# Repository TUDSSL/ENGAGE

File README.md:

# Battery-Free Game Boy

This is the official public repository for ENGAGE: the battery-free gaming console.
    
## Project Overview

### Rationale

Battery-free devices can [make phone calls](https://dl.acm.org/doi/abs/10.1145/3090090), [facilitate machine learning](https://dl.acm.org/doi/10.1145/3411808), or even [track eyes](https://doi.org/10.1145/3241539.3241578), but immersive interactive experience without batteries has not been explored so far. In this project we focus on this ignored part of the battery-free device ecosystem. We explore how reactive and user-centric applications, _mobile gaming_ in particular, can also be battery-free.	

### The Basic Problem of Gaming without Batteries: Power Failures 

Powering small embedded computer only with energy harvesting would cause frequent power failures, resulting in a constant restart of a long-running application. Let us look at the above figure which symbolically represents an execution of a [Tetris](https://en.wikipedia.org/wiki/Tetris) game on a battery-free platform powered by harvested (fluctuating) energy. Without any protection against power failures the game would play until energy is lost (i.e. at line 185) and then would restart from the loading screen. [Intermittent computing techniques](https://drops.dagstuhl.de/opus/volltexte/2017/7131/pdf/LIPIcs-SNAPL-2017-8.pdf) would protect from this unwanted behaviour: after a power failure, line 186 would be executed proceeding from the exact system state as before the power failure. This way a game state will resume at the exact frame where the play ended due to power failure (in other words, [tetromino](https://en.wikipedia.org/wiki/Tetromino) will be in the same place when the game resumes).

### System Design: Game Boy Emulation and System State Checkpointing

We designed a Nintendo Game Boy emulator, which we call _Energy Aware Gaming (ENGAGE)_ platform, as a proof of concept that interactive systems powered by only by (intermittently-available) energy harvesting is possible. ENGAGE is build around four key components (see also figure above):

1. **Game emulation:** Use processor emulation to play (Game Boy) retro games to resemble classic [Game Boy](https://en.wikipedia.org/wiki/Game_Boy) platform feel;
1. **Kernel:** Efficiently checkpoint minimal game state to the dedicated non-volatile memory to protect from a restart after a power failure, enabling continuous game play;
1. **Energy:** Power battery-free gaming console from gaming actions (button presses) and from ambient solar energy and store this energy in a small capacitor;
1. **Hardware:** Exploit leading (but off-the-shelf and accessible to everyone) [low-power 32-bit ARM Cortex M4 microcontroller](https://ambiq.com/apollo3-blue/) and [external FRAM](https://www.fujitsu.com/global/documents/products/devices/semiconductor/fram/lineup/MB85RS4MT-DS501-00053-1v0-E.pdf) to support checkpointing system.

### Hardware

ENGAGE internal PCB is depicted on the above figure (left-hand side: front, right-hand side: back) with the main components (A) [Ambiq Apollo3 Blue ARM Cortex-M4 MCU](https://ambiq.com/apollo3-blue/), (B) [Fujitsu MB85RS4MT 512 KB FRAM](https://www.fujitsu.com/global/documents/products/devices/semiconductor/fram/lineup/MB85RS4MT-DS501-00053-1v0-E.pdf), (C) [ZF AFIG-0007 energy harvesting switch](https://nl.mouser.com/datasheet/2/833/Energy_Harvesting_Generator_US-1075748.pdf), (D) [Semiconductor Components Industries NSR1030QMUTWG low forward voltage diode bridge](https://www.onsemi.com/pub/Collateral/NSR1030QMU-D.PDF), (E) micro USB debugging port, (F) display connector, (G) solar panels connector, (H) cartridge interface, (I) [Texas Instruments BQ25570 harvester/power manager](https://www.ti.com/lit/ds/symlink/bq25570.pdf), and (J) [Texas Instruments TPS61099 boost converter](https://www.ti.com/lit/ds/symlink/tps61099.pdf).

The specific internals of ENGAGE are as follows.

**Microcontroller:** ENGAGE is based on [ARM MCU architecture](https://en.wikipedia.org/wiki/ARM_architecture), a departure from [Texas Instruments MSP430 FRAM series](https://www.ti.com/lit/an/slaa498b/slaa498b.pdf) microcontrollers typically used in [intermittent computing systems](https://drops.dagstuhl.de/opus/volltexte/2017/7131/pdf/LIPIcs-SNAPL-2017-8.pdf). Specifically, we have used [Ambiq Apollo3 Blue ARM Cortex-M4](https://ambiq.com/apollo3-blue/) (operating at a clock frequency of 96 MHz) chosen for its best-in-class energy efficiency. Apollo3 MCU (marked as (A) in the above figure) runs the Game Boy emulator and [checkpointing software](https://github.com/TUDSSL/ENGAGE/tree/master/software).

**Memory:** A fast, byte-addressable, non-volatile memory is crucial to enable saving and restoring ENGAGE state (in other words, game state) in spite of power failures. To enable this, we equipped ENGAGE with an external dedicated FRAM IC: [Fujitsu MB85RS4MT 512 KB FRAM](https://www.fujitsu.com/global/documents/products/devices/semiconductor/fram/lineup/MB85RS4MT-DS501-00053-1v0-E.pdf), marked as (B) in the above figure, connected through SPI to the MCU providing a fast (enough) and durable method of non-volatile storage for checkpoints.

**Energy Harvesting:** We extract energy from two sources: (i) button presses, using six mechanical off-the-shelf [ZF AFIG-0007 energy harvesting switches](https://nl.mouser.com/datasheet/2/833/Energy_Harvesting_Generator_US-1075748.pdf) - four switches at the D-pad and one switch per "A" and "B" button (see (C) in the above figure), and (ii) a set of [Panasonic AM-1417CA amorphous silicon solar cells](https://www.panasonic-electric-works.com/cps/rde/xbcr/pew_eu_en/ca_amorton_solar_cells_en.pdf) attached to the front of the Game Boy chassis. Solar panels are managed by [Texas Instruments BQ25570 harvester/power manager](https://www.ti.com/lit/ds/symlink/bq25570.pdf). Harvested energy is stored in a 3.3 mF capacitor.

**Cartridges:** To be able to read Game Boy game cartridges, a cartridge connector is placed on the back of the ENGAGE platform PCB (marked as (H) in the above figure). The cartridge interfaces with the MCU using [Semtech SX1503 I/O expanders](https://www.mouser.com/datasheet/2/761/sx150x-1283306.pdf). This extender translates the 3V system voltage to 5V logic required by the cartridge.

**Display:** It was difficult to source a large display that had reasonable power requirements, a decent refresh rate, and minimal external driving circuitry. We quickly discarded the use of electronic ink displays because of its slow refresh rate and complex driving circuitry. Instead we use a 26.02 × 27.82 mm [Japan Display LPM013M126A LCD](https://www.j-display.com/product/pdf/Datasheet/4LPM013M126A_specification_Ver02.pdf). The display is is smaller than the original Game Boy screen (47 × 43 mm) but has a better resolution of 176 × 176 pixels compared to original 160 × 144 pixel matrix.

### Checkpointing

The core software component of ENGAGE is differential checkpointing library called _MPatch_ located in [software/libs/mpatch](https://github.com/TUDSSL/ENGAGE/blob/master/software/libs/mpatch) folder of this repository. Further description of MPatch is provided in a separate [document](https://github.com/TUDSSL/ENGAGE/blob/master/software/libs/mpatch/README.md).

## Getting Started

This repository contains everything required to build your own Battery-Free Game Boy. Below we describe how to build your own ENGAGE hardware and software.

### Building the Hardware

Hardware-related sources are stored in the following folders.

 - [/enclosure](https://github.com/TUDSSL/ENGAGE/tree/master/enclosure): Complete set of [3D STL files](https://en.wikipedia.org/wiki/STL_%28file_format%29) of the complete ENGAGE enclosure (front, back, buttons, D-pad, LCD holder)
 - [/hardware/main-board](https://github.com/TUDSSL/ENGAGE/tree/master/hardware/main-board): Main ENGAGE board [KiCad](https://kicad.org/) files. Specifically, the folder contains `.gbr` Gerber output files for manufacturing, `.drl` drill file for manufacturing, schematics of the PCB in `.pdf` format, `.csv` file with bill of materials and the KiCad project files `.kicad_pcb`, `.pro` and `.sch`.
 - [/hardware/apollo-3-module](https://github.com/TUDSSL/ENGAGE/tree/master/hardware/apollo-3-module): As above, but for the de-attachable board with the MCU and FRAM (see above figure - component (A) and (B))
 
 Enclosure can be printed using your favorite 3D printer or you can send all [/enclosure](https://github.com/TUDSSL/ENGAGE/tree/master/enclosure) files to one of online-available 3D printing services. As for the PCBs, you can either assemble everything yourself or send all [/hardware](https://github.com/TUDSSL/ENGAGE/tree/master/hardware/) files to many online-available PCB assembly companies for production. 

### Building the Software

Software-related sources are stored in the following folders.

- [/software/apps](https://github.com/TUDSSL/ENGAGE/tree/master/software/apps): Applications' source code folder containing three applications:
    - [emulator](https://github.com/TUDSSL/ENGAGE/tree/master/software/apps/emulator): main application of ENGAGE emulator, which can be also used to reproduce [results of the paper](#How-to-Cite-This-Work);
    - [checkpoint](https://github.com/TUDSSL/ENGAGE/tree/master/software/apps/checkpoint): application to test the performance of checkpointing mechanism;
    - [memtracker](https://github.com/TUDSSL/ENGAGE/tree/master/software/apps/memtracker): application to test the performance of memory use tracking mechanism;
- [/software/config](https://github.com/TUDSSL/ENGAGE/tree/master/software/config): Various configuration files.
- [/software/external](https://github.com/TUDSSL/ENGAGE/tree/master/software/external): External dependencies to the project, such as MCU SDK.
- [/software/libs](https://github.com/TUDSSL/ENGAGE/tree/master/software/libs): Set of core libraries handling I/O (that is [console buttons](https://github.com/TUDSSL/ENGAGE/tree/master/software/libs/buttons), [game cartridge](https://github.com/TUDSSL/ENGAGE/tree/master/software/libs/cartridge), [console display](https://github.com/TUDSSL/ENGAGE/tree/master/software/libs/display), [Game Boy emulator](https://github.com/TUDSSL/ENGAGE/tree/master/software/libs/emulator), [FRAM access](https://github.com/TUDSSL/ENGAGE/tree/master/software/libs/fram)) and checkpointing (that is [just-in-time checkpoint](https://github.com/TUDSSL/ENGAGE/tree/master/software/libs/jit), [memory state tracker](https://github.com/TUDSSL/ENGAGE/tree/master/software/libs/memtracker), and [MPatch checkpointing](https://github.com/TUDSSL/ENGAGE/tree/master/software/libs/mpatch)).
- [/software/platforms](https://github.com/TUDSSL/ENGAGE/tree/master/software/platforms): GPIO pin mappings.
- [/software/scripts](https://github.com/TUDSSL/ENGAGE/tree/master/software/scripts): Scripts pertaining to the build process.

#### Note on the Game Boy Emulator

We do not provide the copy of the Game Boy emulator in this repository. Our build system (using [/software/scripts](https://github.com/TUDSSL/ENGAGE/tree/master/software/scripts)) automatically downloads and patches (applying optimizations and improvements) an external, not written by us, Game Boy emulator. Specifically, we have used [Game Boy emulator](https://mikrocontroller.bplaced.net/wordpress/?page_id=1290) for [STM32F746 Discovery board](https://www.st.com/en/evaluation-tools/32f746gdiscovery.html) written by [Uwe Becker](https://mikrocontroller.bplaced.net/wordpress/?page_id=8).

#### Build Process

After cloning this repository to your local computer the following instructions can be used to generate the ENGAGE binaries. From the project directory execute the following.

```bash
$ cd software/build
$ cmake ..
$ make install

```

Then using your favorite debugger (we have used one of [SEGGER J-Link debug probes](https://www.segger.com/products/debug-probes/j-link/models/model-overview/) for this project) the ENGAGE binaries (stored in the [/software/bin](https://github.com/TUDSSL/ENGAGE/tree/master/software/bin) folder) can be uploaded to the MCU using a debugger whilst powering the platform using USB. The main binary is called `emulator` whilst the others provide a means to reproduce the results obtained in the [paper](#How-to-Cite-This-Work). After this step a [game cartridge can be loaded](#Load-Game-Cartridge).

#### Last Tested Software Versions

This software was build successfully using the following software versions.

- [CMake](https://cmake.org/download/) version 3.18.4
- [arm-none-eabi-gcc](https://gcc.gnu.org/) version 10.2.0
- [arm-none-eabi-newlib](https://www.sourceware.org/newlib/) version 3.3.0
- [arm-none-eabi-binutils](https://www.gnu.org/software/binutils/) version 2.35

## How to Operate ENGAGE

There are two important operations when using ENGAGE that are not related to normal gaming: **loading game cartridge** and **system reset**, both described below.

### Load Game Cartridge

After programming the [emulator binary](https://github.com/TUDSSL/ENGAGE/tree/master/software/bin) to ENGAGE, a Game Boy cartridge with your favorite game needs to be loaded to ENGAGE. To load a cartridge, first put the physical cartridge in the cartridge slot (at the back of ENGAGE) and then hold down **Start** and **A** buttons on ENGAGE while powering ENGAGE through the USB port. You can let go **Start** and **A** buttons after a few seconds. When loading of the cartridge has completed the game will start. Note that there is currently [no progress indication](https://github.com/TUDSSL/ENGAGE/issues/4) of this operation on the screen of ENGAGE. Remember that the process can take five minutes (or more) for large cartridges! After a cartridge has been loaded it can be removed from the device.

### System Reset

Due to the unique nature of ENGAGE's state resuming after power failure, resetting ENGAGE requires a unique key combination (unlike the original Game Boy that you could turn off and on again easily). This reset is performed by holding **Start** and **Select** buttons while powering ENGAGE through an USB port. Please note that this reset operation does *not* require you to reload the game cartridge.

## Frequently Asked Questions

- **When the energy source is changed from solar to button-mashing, how long is ENGAGE temporarily off?**

We actually harvest from both energy sources at the same time! We developed a circuit that manages this internally. However, this still means that the user will experience interruptions of play, that can vary between sub-second (in extreme well outdoor light conditions) to many seconds (on a gloomy day, indoors). While the button presses generate extra energy to sustain game play, most of the energy is still generated by solar panels. More discussion on this can be found in our [research paper](#How-to-Cite-This-Work). 

- **How do the buttons generate power?**

The buttons generate power by moving a small but powerful magnet inside a tightly wound wire coil. The change in the magnetic field generates power. When you press the button (and when you release) it moves the magnet through the coil, this energy is then siphoned into a capacitor for immediate use by the ENGAGE hardware to support all activities. Because of advances in manufacturing over the past decade the magnet and coil are so small that they can fit inside a button that is acceptable to a user.

- **Why is the screen so small?**

Yes, the screen is smaller that in the original Game Boy (which is a [source of complaints](https://www.reddit.com/r/gadgets/comments/in3aco/batteryfree_game_boy_runs_off_of_solar_and/) of many internauts), but the one we [used in the initial ENGAGE design](https://www.j-display.com/product/pdf/Datasheet/4LPM013M126A_specification_Ver02.pdf) the best one we could find in terms of resolution and energy consumption. If you have a better screen to suggest, then make a new [project issue](#How-to-Contribute-to-this-Project) and send us a [pull request](#How-to-Contribute-to-this-Project).

- **Can ENGAGE play sound?**

Unfortunately not. Sound generation costs extra energy and as we operate on a very thin energy budget we had to make choices which features of original Game Boy had to be excluded from ENGAGE.

- **Can I buy one?**

Unfortunately not. But you can build one! All hardware and software of ENGAGE, together with the process of how to make it run is simply in _this repository_. Please remember that ENGAGE **was not (and is not meant to be) a product we can sell**. This is a research project and a concept demonstration.

## How to Contribute to this Project

We look forward to your contributions, improvements, additions and changes. Please follow the standard [GitHub flow](https://docs.github.com/en/free-pro-team@latest/github/collaborating-with-issues-and-pull-requests/github-flow) for code contributions. In macro terms this means the following.

1. [Fork the `master` branch](https://docs.github.com/en/free-pro-team@latest/github/getting-started-with-github/fork-a-repo#keep-your-fork-synced)  of this repository; make sure that your fork will be [up to date](https://docs.github.com/en/free-pro-team@latest/github/getting-started-with-github/fork-a-repo#keep-your-fork-synced) with the latest `master` branch.
1. Create an issue [here](https://github.com/TUDSSL/ENGAGE/issues) with a new feature or a bug report.
1. Perform changes on your local branch and [push them to your forked clone](https://docs.github.com/en/free-pro-team@latest/github/collaborating-with-issues-and-pull-requests/merging-an-upstream-repository-into-your-fork).
1. Create a [pull request](https://docs.github.com/en/free-pro-team@latest/github/collaborating-with-issues-and-pull-requests/creating-a-pull-request) referencing the issue it covers and wait for our response.

### List of Known Issues

List of all known issues is listed in the [Issues](https://github.com/TUDSSL/ENGAGE/issues) list of this project. If you found a bug or you would like to enhance ENGAGE: [please contribute](#How-to-Contribute-to-this-Project)! We look forward to your additions. Let ENGAGE grow and become a better and **more sustainable** gaming experience.

## How to Cite This Work

The results of this project have been published in a peer-reviewed academic publication (from which all technical figures in this file originate). Details of the publication are as follows.

* **Authors and the project team:** [Jasper de Winkel](https://jasperdewinkel.com/), [Vito Kortbeek](https://www.vitokortbeek.com/), [Josiah Hester](https://josiahhester.com/), [Przemysław Pawełczak](http://www.pawelczak.net/)
* **Publication title:** _Battery-Free Game Boy_
* **Pulication venue:** [Proceedings of the ACM on Interactive, Mobile, Wearable and Ubiquitous Technologies, Volume 4, Issue 3, September 2020](https://dl.acm.org/toc/imwut/2020/4/3) and [Proceedings of ACM UbiComp 2020](https://ubicomp.org/ubicomp2020/)
* **Link to publication:** https://doi.org/10.1145/3411839 (Open Access)
* **Link to ACM UbiComp 2020 conference presentation video:** https://www.youtube.com/watch?v=XxjrTHBFBSM

To cite this publication please use the following BiBTeX entry.

```
@article{dewinkel:imwut:2020:gameboy,
  title = {Battery-Free Game Boy},
  author = {Jasper {de Winkel} and Vito {Kortbeek} and Josiah {Hester} and Przemys{\l}aw {Pawe{\l}czak}},
  journal = {Proc. ACM Interact. Mob. Wearable Ubiquitous Technol.},
  volume = {4},
  number = {3},
  pages = {111:1--111:34},
  year = {2020},
  publisher = {ACM}
}
```

## Related Websites

* **Project source code:** https://github.com/tudssl/engage (this repository)
* **Project announcement website:** https://www.freethegameboy.info

## The Press

The project has been covered extensively by international media. Here is the list of example posts and articles (as of October 30, 2020).

[CNET](https://www.cnet.com/features/the-first-battery-free-game-boy-wants-to-power-a-gaming-revolution/), [The Wall Street Journal](https://www.wsj.com/articles/battery-free-energy-harvesting-perpetual-machines-the-weird-future-of-computing-11601697600?st=xyjz99iomamhwr6&reflink=article_copyURL_share), [Mashable](https://mashable.com/video/battery-free-gameboy/), [Hackaday](https://hackaday.com/2020/09/11/game-boy-plays-forever/), [The Verge](https://www.theverge.com/tldr/2020/9/4/21422605/engage-battery-free-game-boy-button-mashing-solar-panels-research-environmental-sustainability), [Gizmodo](https://earther.gizmodo.com/this-battery-free-game-boy-is-the-first-step-toward-ens-1844953062), [Engadget](https://www.engadget.com/engage-game-boy-211023869.html), [PCMag](https://www.pcmag.com/news/solar-powered-game-boy-provides-infinite-play), [The Register](https://www.theregister.com/2020/09/04/battery_free_gameboy/), [Tech Times](https://www.techtimes.com/articles/252268/20200903/game-boy-gaming-console-battery-free-play-want-without-recharging.htm), [Nintendo Life](https://www.nintendolife.com/news/2020/09/this_battery-free_game_boy_could_be_the_future_of_portable_tech), [Daily Mail](https://www.dailymail.co.uk/sciencetech/article-8695791/Battery-free-Game-Boy-charged-MILLIONS-times-sun-pressing-buttons.html), [The Independent](https://www.independent.co.uk/life-style/gadgets-and-tech/news/game-boy-battery-free-technology-renewable-power-a9705256.html), [r/gadgets](https://www.reddit.com/r/gadgets/comments/in3aco/batteryfree_game_boy_runs_off_of_solar_and/)

## Acknowledgments

This research project was supported by [Netherlands Organisation for Scientific Research](https://www.nwo.nl/en), partly funded by the [Dutch Ministry of Economic Affairs and Climate Policy](https://www.government.nl/ministries/ministry-of-economic-affairs-and-climate-policy), through [TTW Perspective program ZERO (P15-06)](https://www.nwo.nl/en/researchprogrammes/perspectief/previous-awards/zero-towards-energy-autonomous-systems-iot) within Project P1 and P4, and by the [National Science Foundation](https://www.nsf.org/) through grants [CNS-1850496](https://www.nsf.gov/awardsearch/showAward?AWD_ID=1850496) and [CNS-2032408](https://www.nsf.gov/awardsearch/showAward?AWD_ID=2032408). Any opinions, findings, and conclusions or recommendations expressed in this material are those of the author(s) and do not necessarily reflect the views of the National Science Foundation.

## Copyright

Copyright (C) 2020 TU Delft Embedded and Networked Systems Group/Sustainable Systems Laboratory.

MIT License or otherwise specified. See [license](https://github.com/TUDSSL/ENGAGE/blob/master/LICENSE) file for details.

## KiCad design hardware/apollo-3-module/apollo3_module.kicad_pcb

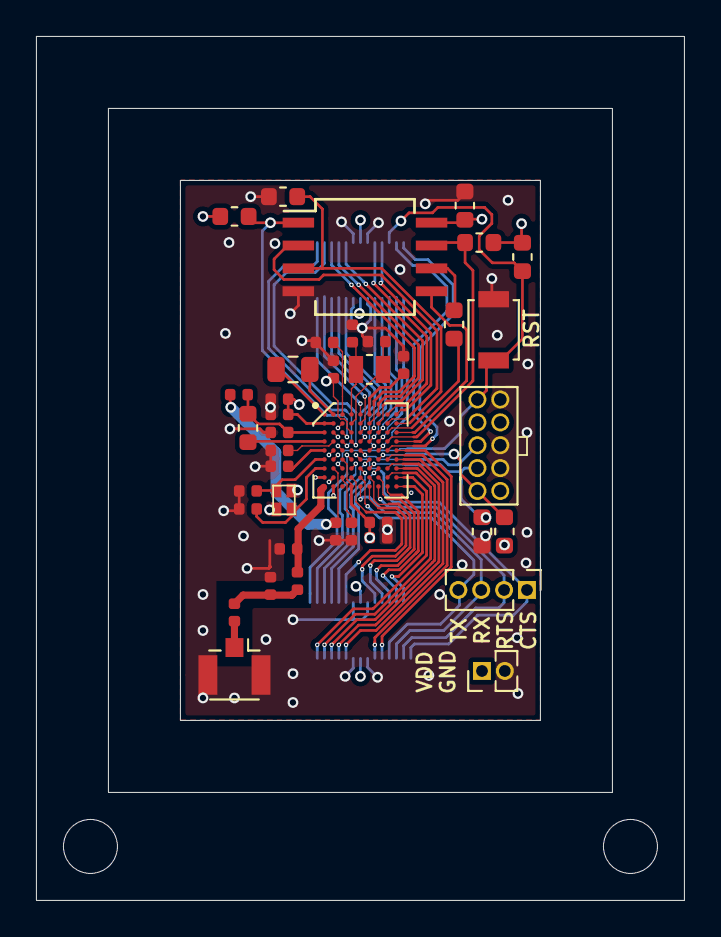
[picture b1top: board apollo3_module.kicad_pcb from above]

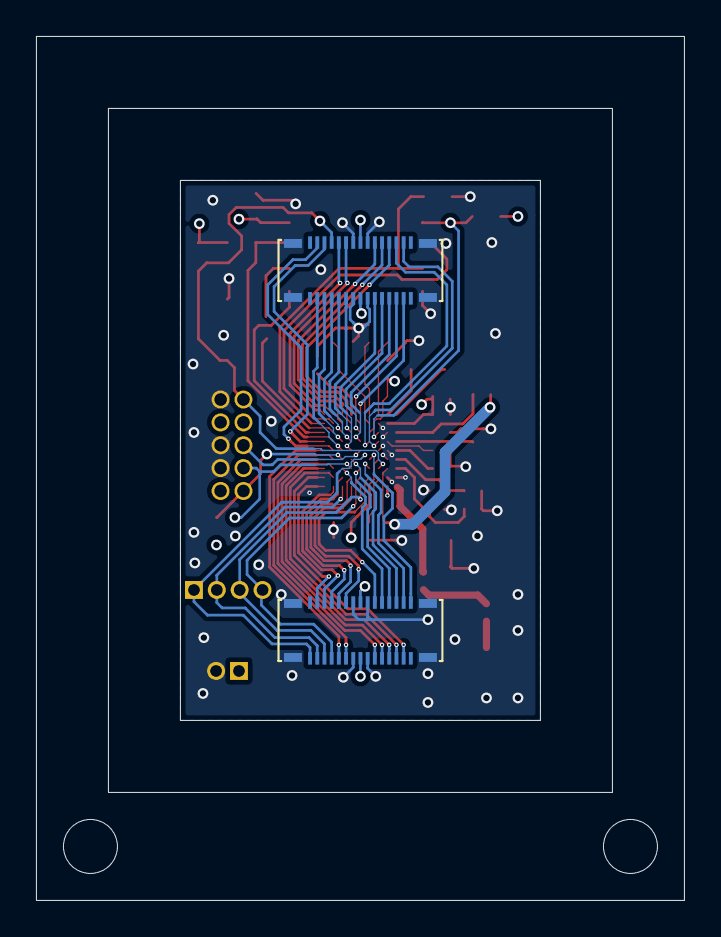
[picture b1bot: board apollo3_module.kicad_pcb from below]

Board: 4 copper layers, 36.0 x 48.0 mm, 44 parts (2 on the bottom side), 71 nets.

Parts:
C1, C5, C10, C11, C15: 1uF; C_0402_1005Metric
C2, C4, C13, C17, C18: DNP; C_0402_1005Metric
C3: 470nF; C_0402_1005Metric
C6: 47nF; C_0402_1005Metric
C7, C8, C9, C16: 2.2uF; C_0402_1005Metric
C12: 0.5pF; C_0402_1005Metric
C14: 4.7uF; C_0402_1005Metric
C19: 1uF; C_0603_1608Metric
H1, H2: eC_Registration; eC_Mount
J1, J2: 51338-0374
J3: Conn_01x04; PinHeader_1x04_P1.27mm_Vertical
J4: SWD_10; FTSH-105-01-F-D-K
J5: Conn_Coaxial; U.FL_Hirose_U.FL-R-SMT-1_Vertical
J6: Conn_01x02; PinHeader_1x02_P1.27mm_Vertical
L1: 2.2uH; L_0805_2012Metric
L2: 1uH; L_0603_1608Metric
L3: 2.7nH; L_0402_1005Metric
L4: 2nH; L_0402_1005Metric
R1: 0; R_0603_1608Metric
R2, R6, R7, R8: DNP; R_0603_1608Metric
R3: 0; R_0402_1005Metric
R4, R5: 10k; R_0603_1608Metric
SW1: B3U-1000P; SW_SPST_B3U-1000P
U1: APOLLO3; BGA-81_9x9_5.0x5.0mm
U2: MB85RS4MT; SO-8_5.3x6.2mm_P1.27mm
Y1: ECS-320-8-47-JTN; ECX-1247
Y2: ABS06W-32.678kHz-D-2; Crystal_SMD_MicroCrystal_CC8V-T1A-2Pin_2.0x1.2mm

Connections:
/DBG_CTS: J1.29, J3.1, U1.F5
/DBG_RTS: J1.27, J3.2, U1.J7
/DBG_RX: J1.25, J3.3, U1.J5
/DBG_TX: J1.23, J3.4, U1.H5
/FRAM_HOLD: R6.2, U1.D8, U2.7
/FRAM_WP: R7.1, U1.B9, U2.3
/G0: J1.12, U1.H4
/G1: J1.4, U1.G4
/G2: J1.2, U1.F4
/G3: J1.8, U1.G5
/G4: J2.26, U1.D9
/G5: J1.21, U1.E9
/G6: J2.28, U1.E8
/G7: J1.11, U1.F9
/G8: J1.19, U1.F8
/G9: J1.10, U1.G7
/G10: J1.9, U1.G8
/G11: J2.5, U1.B5
/G12: J2.10, U1.A7
/G13: J2.12, U1.B7
/G14: J2.25, U1.D7
/G15: J2.23, U1.C7
/G16: J2.6, U1.D4
/G17: J2.4, U1.D3
/G18: J2.9, U1.C5
/G25: J2.20, U1.A8
/G28: J2.22, U1.A9
/G29: J2.3, U1.A5
/G30: J1.6, U1.F6
/G31: J2.7, U1.D5
/G32: J2.11, U1.E6
/G33: J2.8, U1.B6
/G34: J2.19, U1.C6
/G35: J2.21, U1.D6
/G36: J1.22, U1.H6
/G37: J1.24, U1.H7
/G38: J1.20, U1.J6
/G39: J1.26, U1.J8
/G40: J1.28, U1.J9
/G46: J2.27, U1.E7
/G47: J1.3, U1.H9
/G48: J1.7, U1.G9
/G49: J1.5, U1.H8
/MSPI_CE0: R8.2, U1.C3, U2.1
/MSPI_CLK: R1.2, U2.6
/MSPI_MISO: U1.B8, U2.2
/MSPI_MOSI: U1.C9, U2.5
/SWDCK: J4.4, R4.1, U1.G6
/SWDIO: J4.2, R5.2, U1.F7
/SWO: J4.6, U1.E5
/nRST: J2.24, J4.10, R2.2, SW1.1, U1.G3
GND: C1.1, C2.2, C3.2, C4.2, C5.1, C6.2, C7.1, C8.1, C9.1, C10.1, C11.1, C12.2, C13.2, C14.2, C15.2, C16.1, C17.2, C18.1, C19.1, J1.13, J1.14, J1.17, J1.18, J1.31, J2.13, J2.14, J2.17, J2.18, J2.31, J4.3, J4.5, J4.9, J5.2, J6.2, R4.2, R7.2, SW1.2, U1.B3, U1.C2, U1.E2, U1.E3, U1.F2, U1.H1, U1.H2, U1.J2, U2.4, Y1.2, Y1.4
unnamed: C2.1, U1.G1, Y1.1
unnamed: C3.1, U1.A6
unnamed: C4.1, L3.1, U1.J1
unnamed: C6.1, U1.H3
unnamed: C7.2, U1.A3
unnamed: C8.2, U1.D2
unnamed: C9.2, U1.E1
unnamed: C12.1, L3.2, L4.1
unnamed: C13.1, U1.F1, Y1.3
unnamed: C14.1, L2.2, R3.1, U1.C1
unnamed: C15.1, R3.2, U1.G2
unnamed: C17.1, U1.A4, Y2.1
unnamed: C18.2, U1.B4, Y2.2
unnamed: J5.1, L4.2
unnamed: L1.1, U1.A1
unnamed: L1.2, U1.A2
unnamed: L2.1, U1.D1
unnamed: R1.1, U1.C8
VDD: C1.2, C5.2, C10.2, C11.2, C16.2, C19.2, J1.15, J1.16, J2.15, J2.16, J4.1, J6.1, R2.1, R5.1, R6.1, R8.1, U1.B1, U1.B2, U1.C4, U1.F3, U1.J4, U2.8

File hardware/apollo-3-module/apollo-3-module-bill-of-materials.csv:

Item,Qty,Reference(s),Value,Datasheet,Partnum
1,5,"C1, C5, C10, C11, C15",1uF,~,GRM155C81A105KA12D
2,5,"C2, C4, C13, C17, C18",DNP,~,
3,1,C3,470nF,~,GRT155R61C474KE01D
4,1,C6,47nF,~,GRM155R71E473KA88D
5,4,"C7, C8, C9, C16",2.2uF,~,GRM155R61C225KE11D
6,1,C12,0.5pF,~,GRM1885C1HR50BA01D
7,1,C14,4.7uF,~,CL05A475KP5NRNC
8,1,C19,1uF,~,TMK107B7105KA-T
9,2,"H1, H2",eC_Registration,https://www.eurocircuits.com/ec-registration-system/,
10,2,"J1, J2",51338-0374,https://www.molex.com/webdocs/datasheets/pdf/en-us/051338037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,51338-0374
11,1,J3,Conn_01x04,~,GRPB041VWVN-RC
12,1,J4,SWD_10,http://infocenter.arm.com/help/topic/com.arm.doc.ddi0314h/DD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,FTSH-105-01-F-D-K
13,1,J5,Conn_Coaxial, ~,U.FL-R-SMT-1
14,1,J6,Conn_01x02,~,GRPB021VWVN-RC
15,1,L1,2.2uH,~,DFE201610E-2R2M=P2
16,1,L2,1uH,~,DFE18SAN1R0MG0L
17,1,L3,2.7nH,~,LQG15HS2N7S02D
18,1,L4,2nH,~,LQG15HS2N0S02D
19,1,R1,0,~,ERJ-3GEY0R00V
20,4,"R2, R6, R7, R8",DNP,~,
21,1,R3,0,~,ERJ-2GE0R00X
22,2,"R4, R5",10k,~,ERJ-3GEYJ103V
23,1,SW1,B3U-1000P,~,B3U-1000P
24,1,U1,APOLLO3,https://www.ambiqmicro.com/static/mcu/files/Apollo3_Blue_MCU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,AMA3B1KK-KBR-B0
25,1,U2,MB85RS4MT,https://www.fujitsu.com/global/documents/products/devices/se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,MB85RS4MT
26,1,Y1,ECS-320-8-47-JTN,https://nl.mouser.com/datasheet/2/122/ECX_1247-220263.pdf,ECS-320-8-47-JTN
27,1,Y2,ABS06W-32.678kHz-D-2,https://abracon.com/Resonators/ABS06W.pdf,ABS06W-32.768kHz-D-2

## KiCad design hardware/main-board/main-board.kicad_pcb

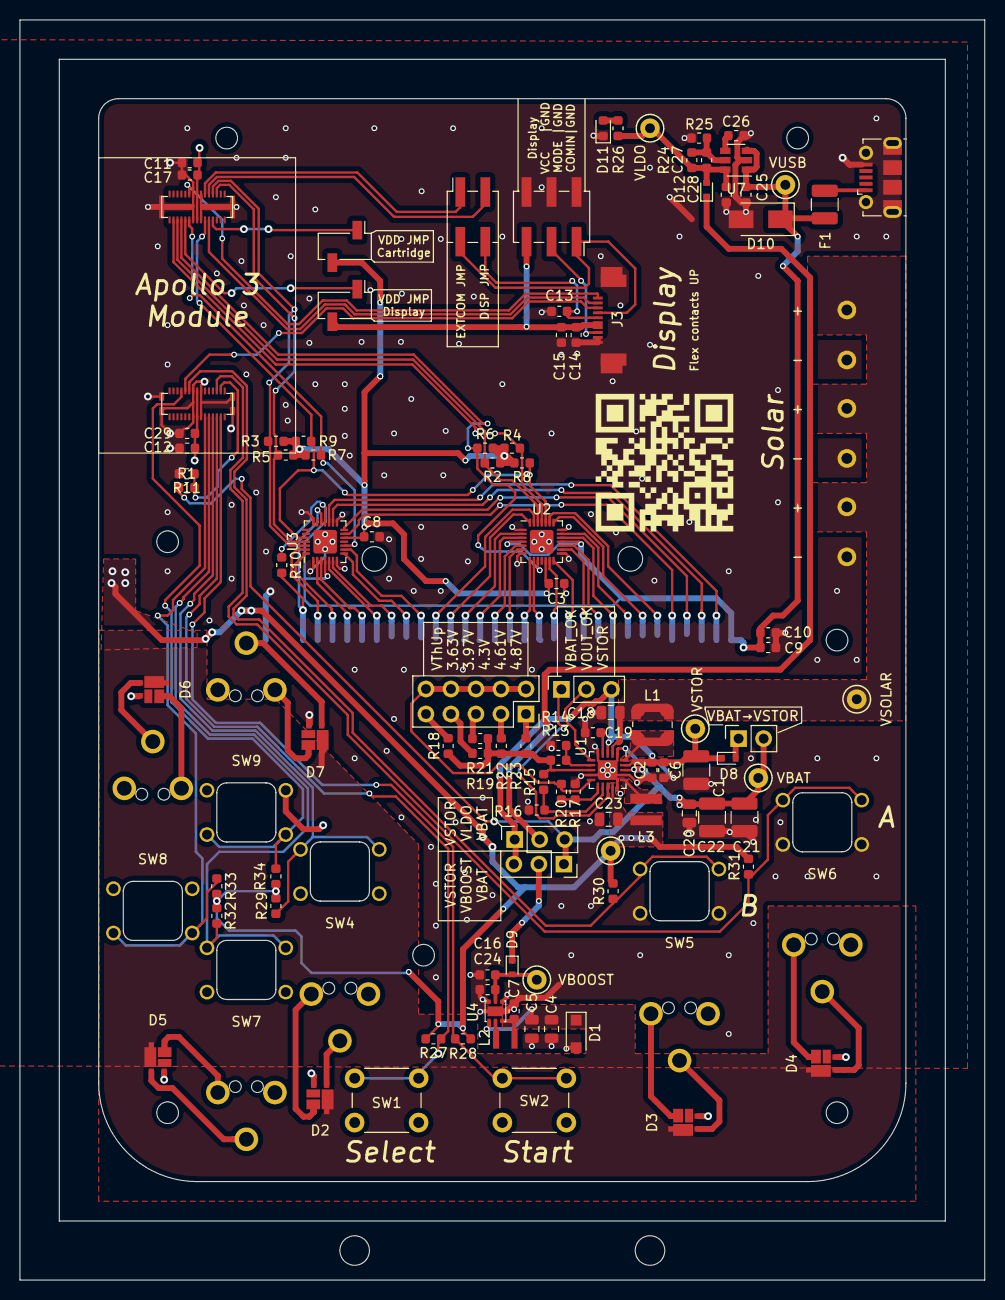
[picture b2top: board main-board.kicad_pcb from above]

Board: 2 copper layers, 98.0 x 128.0 mm, 125 parts (1 on the bottom side), 101 nets.

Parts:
C1, C22: DNP; C_1210_3225Metric
C2, C19, C26: 10nF; C_0603_1608Metric
C3, C8, C9, C13, C17, C29: 100nF; C_0603_1608Metric
C4, C5, C20: DNP; C_0805_2012Metric
C6: 4.7uF; C_0603_1608Metric
C7, C10, C24, C25, C28: 10uF; C_0603_1608Metric
C11, C12, C14, C15: 1uF; C_0603_1608Metric
C16: DNP; C_0603_1608Metric
C18: 4.7uF; C_0805_2012Metric
C21: 100uF; C_1210_3225Metric
C23: 22uF; C_0805_2012Metric
C27: 15pF; C_0603_1608Metric
D1: SZMM3Z5V1ST1G; D_SOD-123F
D2, D3, D4, D5, D6, D7: NSR1030QMUTWG
D8, D9, D12: BAS40-02V-V-G-08; D_SOD-523
D10: 3SMAJ5919B-TP; D_SMA
D11: LED; LED_0603_1608Metric
F1: MF-USMF010; Fuse_1210_3225Metric
H1, H2, H3, H4, H5, H6, H7: MountingHole; MountingHole_2.2mm_M2
H8, H9: eC_Registration; eC_Mount
J1, J2: Conn_01x02; PinSocket_1x02_P2.54mm_Vertical_SMD_Pin1Left
J3: 52745-1097; FPC_10_TOP
J9: GB_CART_CON
J12: Conn_02x02_Odd_Even; PinSocket_2x02_P2.54mm_Vertical_SMD
J14, J19, J20: Conn_01x03; PinSocket_1x03_P2.54mm_Vertical
J15: Conn_02x03_Odd_Even; PinSocket_2x03_P2.54mm_Vertical_SMD
J17: Conn_01x02; PinSocket_1x02_P2.54mm_Vertical
J18: Conn_02x05_Odd_Even; PinSocket_2x05_P2.54mm_Vertical
J21: USB_B_Micro; USB_Micro-B_Molex-105017-0001
J22, J23, J24: Screw_Terminal_01x02; 282837-2
L1: 744031220; WE_3816
L2: LQH2HPN2R2MJRL; Murata_2520
L3: 744029100; WE_2813
R1, R19: 2M; R_0603_1608Metric
R2, R3, R4, R5, R6, R7, R8, R9: DNP; R_0603_1608Metric
R10, R11, R18, R27, R28, R29, R30, R31, R32, R33, R34: 1M; R_0603_1608Metric
R13: 8.2M; R_0603_1608Metric
R14, R23: 4.7M; R_0603_1608Metric
R15: 7.5M; R_0603_1608Metric
R16: 5.1M; R_0603_1608Metric
R17: 3.6M; R_0603_1608Metric
R20: 6.2M; R_0603_1608Metric
R21: 3M; R_0603_1608Metric
R22: 3.9M; R_0603_1608Metric
R24: 82k; R_0603_1608Metric
R25: 30.1k; R_0603_1608Metric
R26: 560; R_0603_1608Metric
S1: TUD_SSL_QR; TUDSSL
S2: TUD_LOGO; DELFT_LOGO2
SW1, SW2: SW_Push; SW_PUSH_6mm
SW4, SW5, SW6, SW7, SW8, SW9: EH_SWITCH
TP1, TP2, TP3, TP4, TP5, TP6, TP7: TestPoint; TestPoint_Keystone_5000-5004_Miniature
U1: BQ25570; QFN-20-1EP_3.5x3.5mm_P0.5mm_EP2x2mm
U2, U3: SX1503; QFN-28-1EP_4x4mm_P0.4mm_EP2.4x2.4mm
U4: TPS610995DRV; Texas_WSON_6
U5: Apollo-3-module; Apollo-3-Module
U7: TPS79301-EP; SOT-23-6

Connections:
/BTN_SEL: R28.1, SW2.2, U5.34
/BTN_START: R27.1, SW1.2, U5.36
/Cartridge/H_A0: J9.6, U2.23
/Cartridge/H_A1: J9.7, U2.22
/Cartridge/H_A2: J9.8, U2.20
/Cartridge/H_A3: J9.9, U2.19
/Cartridge/H_A4: J9.10, U2.17
/Cartridge/H_A5: J9.11, U2.16
/Cartridge/H_A6: J9.12, U2.14
/Cartridge/H_A7: J9.13, U2.13
/Cartridge/H_A8: J9.14, U2.9
/Cartridge/H_A9: J9.15, U2.8
/Cartridge/H_A10: J9.16, U2.6
/Cartridge/H_A11: J9.17, U2.5
/Cartridge/H_A12: J9.18, U2.3
/Cartridge/H_A13: J9.19, U2.2
/Cartridge/H_A14: J9.20, U2.28
/Cartridge/H_A15: J9.21, U2.27
/Cartridge/H_CLK: J9.2, U3.17
/Cartridge/H_CS: J9.5, U3.13
/Cartridge/H_D0: J9.22, U3.9
/Cartridge/H_D1: J9.23, U3.8
/Cartridge/H_D2: J9.24, U3.6
/Cartridge/H_D3: J9.25, U3.5
/Cartridge/H_D4: J9.26, U3.3
/Cartridge/H_D5: J9.27, U3.2
/Cartridge/H_D6: J9.28, U3.28
/Cartridge/H_D7: J9.29, U3.27
/Cartridge/H_nRD: J9.4, U3.14
/Cartridge/H_nRST: J9.30, R10.2, U3.19
/Cartridge/H_nWR: J9.3, U3.16
/Cartridge/SCL0: R2.1, U2.26, U5.26
/Cartridge/SCL1: R3.1, U3.26, U5.7
/Cartridge/SDA0: R4.1, U2.25, U5.28
/Cartridge/SDA1: R5.1, U3.25, U5.5
/Cartridge/VCC_MCU: C3.1, C8.2, J2.2, R2.2, R3.2, R4.2, R5.2, R6.2, R7.2, R8.2, R9.2, U2.12, U3.12
/Display/CLK: J3.10, U5.19
/Display/DISP: C13.1, J3.6, J12.4
/Display/DISP_EXTMODE: J3.3, J15.3
/Display/EXTCOMIN: J3.7, J12.2, J15.1
/Display/VIN: C14.1, C15.1, J1.2, J3.4, J3.5, J15.5
/Harvester/BTN1: R29.1, SW4.4, SW4.5, U5.38
/Harvester/BTN1/VOUT: C4.1, C5.1, C7.1, D1.1, D2.2, D3.2, D4.2, D5.2, D6.2, D7.2, L2.1, U4.4, U4.6
/Harvester/BTN2: R30.1, SW5.4, SW5.5, U5.49
/Harvester/BTN3: R31.1, SW6.4, SW6.5, U5.35
/Harvester/BTN4: R32.1, SW7.4, SW7.5, U5.40
/Harvester/BTN5: R33.1, SW8.4, SW8.5, U5.42
/Harvester/BTN6: R34.1, SW9.4, SW9.5, U5.53
/Harvester/VBAT: C20.2, C21.2, C22.2, J14.3, J17.2, J20.1, R1.1, TP3.1, U1.18
/Harvester/VBAT_OK: J19.1, U1.13
/Harvester/VOUT_EN: J19.2, U1.6
/Harvester/VSTOR: C1.2, C2.2, C6.2, D8.1, J14.1, J19.3, J20.3, TP2.1, U1.3, U1.19
/MCU/DISP_DISP: J12.3, U5.9
/MCU/DISP_EXTCOMIN: J12.1, U5.11
/MCU/DISP_MOSI: J3.9, U5.10
/MCU/DISP_VCC: J1.1, U5.22
/MCU/DISP_nCS: J3.8, U5.51
/MCU/GMB_VDD: J2.1, U5.8
/MCU/GMB_nINT0: R6.1, U2.10, U5.24
/MCU/GMB_nINT1: R7.1, U3.10, U5.20
/MCU/GMB_nRST: R8.1, R9.1, U2.24, U3.24, U5.12
/USB_VOUT: D12.1, J14.2
/VCC_3V: C11.1, C12.1, C17.1, C23.1, C29.1, L3.2, R27.2, R28.2, R29.2, R30.2, R31.2, R32.2, R33.2, R34.2, TP5.1, U1.14, U5.15, U5.16, U5.45, U5.46
/VCC_5V: C9.1, C10.1, C25.1, D10.1, F1.2, J9.1, R10.1, TP6.1, U2.4, U2.18, U3.4, U3.18, U7.1, U7.3
GND: C1.1, C2.1, C3.2, C4.2, C5.2, C6.1, C7.2, C8.1, C9.2, C10.2, C11.2, C12.2, C13.2, C14.2, C15.2, C16.2, C17.2, C18.1, C19.2, C20.1, C21.1, C22.1, C23.2, C24.2, C25.2, C26.2, C28.2, C29.2, D1.2, D2.4, D3.4, D4.4, D5.4, D6.4, D7.4, D10.2, D11.1, J3.0, J3.1, J3.2, J9.32, J9.33, J15.2, J15.4, J15.6, J21.5, J21.6, J22.2, J23.2, J24.2, R11.2, R14.2, R16.2, R17.2, R25.2, SW1.1, SW2.1, SW4.6, SW4.7, SW5.6, SW5.7, SW6.6, SW6.7, SW7.6, SW7.7, SW8.6, SW8.7, SW9.6, SW9.7, U1.1, U1.5, U1.9, U1.15, U1.17, U1.21, U2.1, U2.7, U2.15, U2.21, U2.29, U3.1, U3.7, U3.15, U3.21, U3.29, U4.1, U4.3, U4.7, U5.13, U5.14, U5.17, U5.18, U5.43, U5.44, U5.47, U5.48, U5.61, U7.2
unnamed: C16.1, C24.1, D9.2, TP4.1, U4.2
unnamed: C18.2, J22.1, J23.1, J24.1, L1.1, TP1.1, U1.2
unnamed: C19.1, U1.4
unnamed: C26.1, U7.4
unnamed: C27.1, C28.1, D12.2, R24.1, R26.1, TP7.1, U7.6
unnamed: C27.2, R24.2, R25.1, U7.5
unnamed: D2.1, SW4.1
unnamed: D2.3, SW4.3
unnamed: D3.1, SW5.1
unnamed: D3.3, SW5.3
unnamed: D4.1, SW6.1
unnamed: D4.3, SW6.3
unnamed: D5.1, SW7.1
unnamed: D5.3, SW7.3
unnamed: D6.1, SW8.1
unnamed: D6.3, SW8.3
unnamed: D7.1, SW9.1
unnamed: D7.3, SW9.3
unnamed: D8.2, J17.1
unnamed: D9.1, J20.2
unnamed: D11.2, R26.2
unnamed: F1.1, J21.1
unnamed: J18.1, R23.2
unnamed: J18.3, R22.2
unnamed: J18.5, R21.2
unnamed: J18.7, R19.2
unnamed: J18.9, R18.2
unnamed: J18.2, J18.4, J18.6, J18.8, J18.10, R20.1, U1.10
unnamed: L1.2, U1.20
unnamed: L2.2, U4.5
unnamed: L3.1, U1.16
unnamed: R1.2, R11.1, U5.33
unnamed: R13.1, R15.1, R18.1, R19.1, R21.1, R22.1, R23.1, U1.8
unnamed: R13.2, R14.1, U1.7
unnamed: R15.2, R16.1, U1.12
unnamed: R17.1, R20.2, U1.11

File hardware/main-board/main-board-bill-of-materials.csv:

Item,Qty,Reference(s),Value,Datasheet,MPN,
1,2,"C1, C22",DNP,~,,
2,3,"C2, C19, C26",10nF,~,06035C103KAT2A,
3,6,"C3, C8, C9, C13, C17, C29",100nF,~,GCM188R71H104KA57D,
4,3,"C4, C5, C20",DNP,~,,
5,1,C6,4.7uF,~,LMK107BJ475KA-T,
6,5,"C7, C10, C24, C25, C28",10uF,~,GRM188R61A106KE69D,
7,4,"C11, C12, C14, C15",1uF,~,CL10B105KP8NNNC,
8,1,C16,DNP,~,,
9,1,C18,4.7uF,~,CL21A475KOFNNNE,
10,1,C21,100uF,~,LMK325BJ107MM-T,
11,1,C23,22uF,~,CL21A226KPCLRNC,
12,1,C27,15pF,~,CC0603JRNPO9BN150,
13,1,D1,SZMM3Z5V1ST1G,https://diotec.com/tl_files/diotec/files/pdf/datasheets/mm3z2v4.pdf,SZMM3Z5V1ST1G,
14,6,"D2, D3, D4, D5, D6, D7",NSR1030QMUTWG,https://www.onsemi.com/pub/Collateral/NSR1030QMU-D.PDF,NSR1030QMUTWG,
15,3,"D8, D9, D12",BAS40-02V-V-G-08,~,BAS40-02V-V-G-08,
16,1,D10,3SMAJ5919B-TP,~,3SMAJ5919B-TP,
17,1,D11,LED,~,LB Q39G-L2OO-35-1,
18,1,F1,MF-USMF010,~,MF-USMF010,
19,7,"H1, H2, H3, H4, H5, H6, H7",MountingHole,~,,
20,2,"H8, H9",eC_Registration,https://www.eurocircuits.com/ec-registration-system/,,
21,2,"J1, J2",Conn_01x02,~,GBC02SABN-M30,
22,1,J3,52745-1097,~,52745-1097,LCD: LPM013M126A or LPM013M126C
23,1,J9,GB_CART_CON,https://aliexpress.com/item/4000290191316.html,,
24,1,J12,Conn_02x02_Odd_Even,~,M20-8760242,
25,3,"J14, J19, J20",Conn_01x03,~,M20-9990345,
26,1,J15,Conn_02x03_Odd_Even,~,M20-8760346,
27,1,J17,Conn_01x02,~,M20-9990246,
28,1,J18,Conn_02x05_Odd_Even,~,M20-9720545,
29,1,J21,USB_B_Micro,https://www.molex.com/pdm_docs/sd/1050170001_sd.pdf,1050170001,
30,3,"J22, J23, J24",Screw_Terminal_01x02,~,282837-2,
31,1,L1,744031220,~,744031220,
32,1,L2,LQH2HPN2R2MJRL,~,LQH2HPN2R2MJRL,
33,1,L3,744029100,~,744029100,
34,2,"R1, R19",2M,~,RC0603FR-072ML,
35,8,"R2, R3, R4, R5, R6, R7, R8, R9",DNP,~,,
36,11,"R10, R11, R18, R27, R28, R29, R30, R31, R32, R33, R34",1M,~,RC0603FR-071ML,
37,1,R13,8.2M,~,CRCW06038M20FKEA,
38,2,"R14, R23",4.7M,~,RC0603FR-074M7L,
39,1,R15,7.5M,~,CRCW06037M50FKEA,
40,1,R16,5.1M,~,CRCW06035M10FKEA,
41,1,R17,3.6M,~,CRCW06033M60FKEA,
42,1,R20,6.2M,~,CRCW06036M20FKEA,
43,1,R21,3M,~,CRCW06033M00FKEA,
44,1,R22,3.9M,~,CRCW06033M90FKEA,
45,1,R24,82k,~,RC0603FR-0782KL,
46,1,R25,30.1k,~,RC0603FR-0730K1L,
47,1,R26,560,~,RC0603FR-07560RL,
48,1,S1,TUD_SSL_QR,,,
49,1,S2,TUD_LOGO,,,
50,2,"SW1, SW2",SW_Push,~,1825910-7,
51,6,"SW4, SW5, SW6, SW7, SW8, SW9",EH_SWITCH,~,AFIG-0007 and RT1105AF160Q,
52,1,U1,BQ25570,http://www.ti.com/lit/ds/symlink/bq25570.pdf,BQ25570RGR,
53,2,"U2, U3",SX1503,https://nl.mouser.com/datasheet/2/761/sx150x-1283306.pdf,SX1503,
54,1,U4,TPS610995DRV,http://www.ti.com/lit/ds/symlink/tps61099.pdf,TPS610995DRV,
55,1,U5,Apollo-3-module,https://www.ambiqmicro.com/static/mcu/files/Apollo3_Blue_MCU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,2 x 55909-0374,
56,1,U7,TPS79301-EP,http://www.ti.com/lit/ds/symlink/tps79333-ep.pdf,TPS79301DBV,
57,6,SOLAR,AM-1417CA,https://www.panasonic-electric-works.com/cps/rde/xbcr/pew_eu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,AM-1417CA,
57,1,DISPLAY,LPM013M126A,https://www.j-display.com/product/pdf/Datasheet/4LPM013M126A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,LPM013M126A,

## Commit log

2020-07-23 Create README.md
    First version of README ready (with note added)
2020-07-23 Create LICENSE
    MIT license created
2020-11-17 initial code version
2020-12-25 Improve README
    Cleaned up a few typos and clarified wording in a couple places.
2022-12-13 Update README.md
    Link to ZERO program updated
2023-03-12 fix typo in readme
2023-04-03 fixed typos across README
2023-04-03 fixed additional typos
2023-04-03 revert "internals" back to "internauts"
2023-10-12 Add CodeQL Workflow for Code Security Analysis
    Add CodeQL Workflow for Code Security Analysis
    This pull request introduces a CodeQL workflow to enhance the security analysis of our repository. CodeQL is a powerful static analysis tool that helps identify and mitigate security vulnerabilities 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
    We added a new CodeQL workflow file (.github/workflows/codeql.yml) that
    - Runs on every push and pull request to the main branch.
    - Excludes queries with a high false positive rate or low-severity findings.
    - Does not display results for th
2023-10-18 Add CodeQL Workflow for Code Security Analysis
    Add CodeQL Workflow for Code Security Analysis
    This pull request introduces a CodeQL workflow to enhance the security analysis of our repository. CodeQL is a powerful static analysis tool that helps identify and mitigate security vulnerabilities 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
    We added a new CodeQL workflow file (.github/workflows/codeql.yml) that
    - Runs on every pull request (functionality to run on every push to main branches is included as a comment for convenience).
    - Runs daily.
    - Excludes queries with a hig

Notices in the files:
README.md:
Copyright:
Copyright (C) 2020 TU Delft Embedded and Networked Systems Group/Sustainable Systems Laboratory.
MIT License or otherwise specified. See [license](https://github.com/TUDSSL/ENGAGE/blob/master/LICENSE) file for details.
To cite this publication please use the following BiBTeX entry.
